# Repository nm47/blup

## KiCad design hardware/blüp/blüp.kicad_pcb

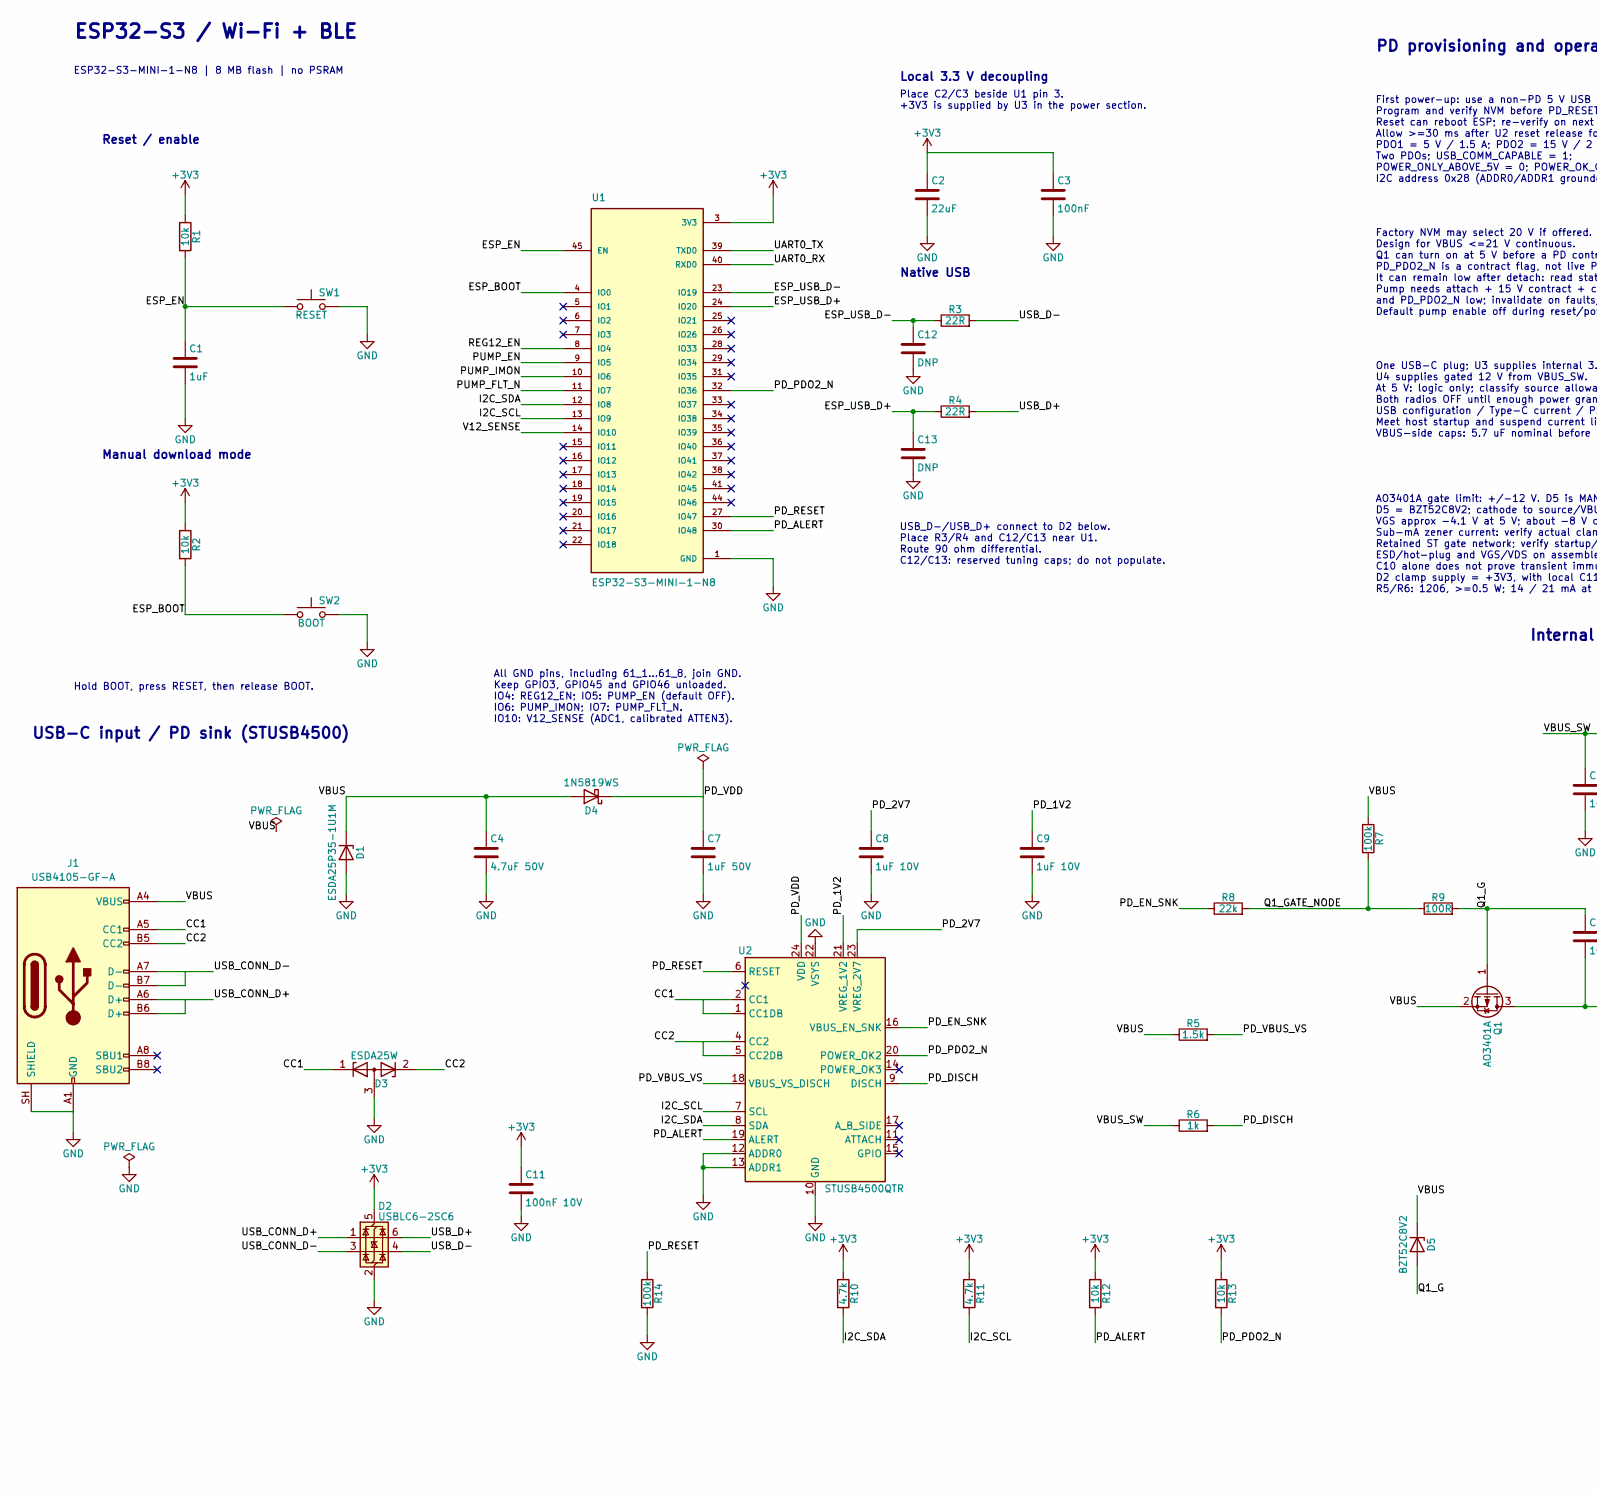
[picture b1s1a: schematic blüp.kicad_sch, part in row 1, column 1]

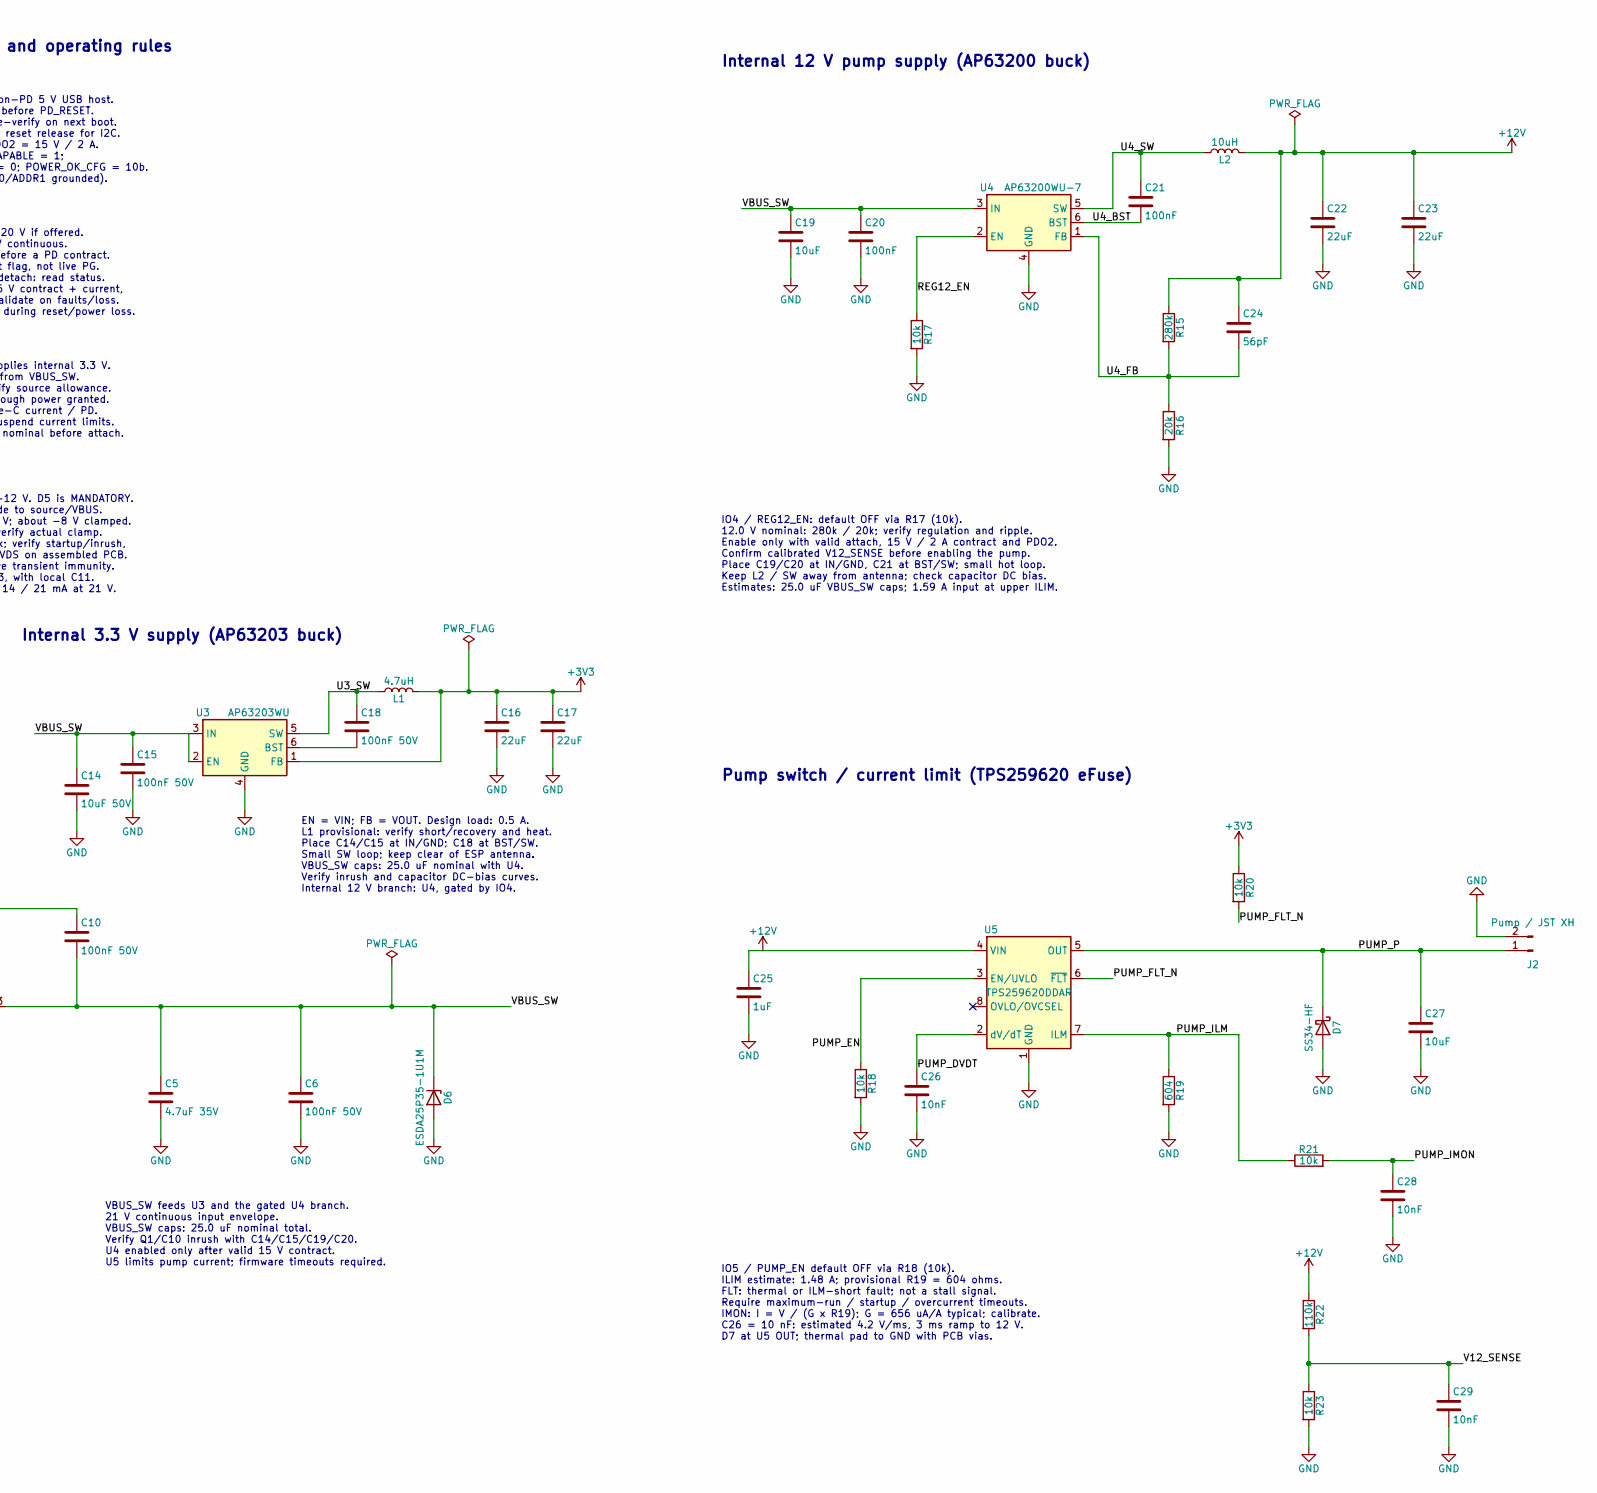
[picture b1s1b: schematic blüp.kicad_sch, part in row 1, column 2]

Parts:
C1: 1uF; C_0603_1608Metric; Tolerance 10%; Voltage 10V
C2, C16, C17: 22uF; C_0805_2012Metric; Tolerance 10%; Voltage 10V
C3: 100nF; C_0603_1608Metric; Tolerance 10%; Voltage 10V
C4: 4.7uF 50V; C_1206_3216Metric; Tolerance 10%; Voltage 50V
C5: 4.7uF 35V; C_1206_3216Metric; Tolerance 10%; Voltage 35V
C6, C10, C15, C18: 100nF 50V; C_0603_1608Metric; Tolerance 10%; Voltage 50V
C7: 1uF 50V; C_0805_2012Metric; Tolerance 10%; Voltage 50V
C8, C9: 1uF 10V; C_0603_1608Metric; Tolerance 10%; Voltage 10V
C11: 100nF 10V; C_0603_1608Metric; Tolerance 10%; Voltage 10V
C12, C13: DNP; C_0603_1608Metric
C14: 10uF 50V; C_1206_3216Metric; Tolerance 10%; Voltage 50V
C19: 10uF; C_1206_3216Metric; Tolerance 10%; Voltage 50V
C20, C21: 100nF; C_0603_1608Metric; Tolerance 10%; Voltage 50V
C22, C23: 22uF; C_1210_3225Metric; Tolerance 10%; Voltage 25V
C24: 56pF; C_0603_1608Metric; Tolerance 5%; Voltage 50V
C25: 1uF; C_0603_1608Metric; Tolerance 10%; Voltage 25V
C26, C28, C29: 10nF; C_0603_1608Metric; Tolerance 10%; Voltage 16V
C27: 10uF; C_1206_3216Metric; Tolerance 10%; Voltage 25V
D1, D6: ESDA25P35-1U1M; ST_QFN-2L_1.6x1.0mm; MPN ESDA25P35-1U1M; LCSC C1974707
D2: USBLC6-2SC6; SOT-23-6; MPN USBLC6-2SC6; LCSC C7519
D3: ESDA25W; SOT-323_SC-70; MPN ESDA25W; LCSC C2935152
D4: 1N5819WS; D_SOD-323; MPN 1N5819WS; LCSC C1884554
D5: BZT52C8V2; D_SOD-123; MPN BZT52C8V2-7-F
D7: SS34-HF; D_SMA; MPN SS34-HF
J1: USB4105-GF-A; USB_C_Receptacle_GCT_USB4105-xx-A_16P_TopMnt_Horizontal; MPN USB4105-GF-A
J2: Pump / JST XH; JST_XH_B2B-XH-A_1x02_P2.50mm_Vertical; MPN B2B-XH-A(LF)(SN)
L1: 4.7uH; L_Bourns-SRN4018; Tolerance 20%; MPN SRN4018-4R7M; LCSC C780206
L2: 10uH; L_Bourns_SRR1260; Tolerance 20%; MPN SRR1260-100M
Q1: AO3401A; SOT-23; MPN AO3401A; LCSC C15127
R1, R2: 10k; R_0603_1608Metric
R3, R4: 22R; R_0603_1608Metric
R5: 1.5k; R_1206_3216Metric; Tolerance 1%
R6: 1k; R_1206_3216Metric; Tolerance 1%
R7, R14: 100k; R_0603_1608Metric; Tolerance 1%
R8: 22k; R_0603_1608Metric; Tolerance 1%
R9: 100R; R_0603_1608Metric; Tolerance 1%
R10, R11: 4.7k; R_0603_1608Metric; Tolerance 1%
R12, R13, R17, R18, R20, R21, R23: 10k; R_0603_1608Metric; Tolerance 1%
R15: 280k; R_0603_1608Metric; Tolerance 1%
R16: 20k; R_0603_1608Metric; Tolerance 1%
R19: 604; R_0603_1608Metric; Tolerance 1%
R22: 110k; R_0603_1608Metric; Tolerance 1%
SW1: RESET; SW_Push_1P1T_XKB_TS-1187A; MPN TS-1187A-B-A-B; LCSC C318884
SW2: BOOT; SW_Push_1P1T_XKB_TS-1187A; MPN TS-1187A-B-A-B; LCSC C318884
U1: ESP32-S3-MINI-1-N8; XCVR_ESP32-S3-MINI-1-N8; MPN ESP32-S3-MINI-1-N8
U2: STUSB4500QTR; QFN-24-1EP_4x4mm_P0.5mm_EP2.7x2.7mm; MPN STUSB4500QTR; LCSC C2678061
U3: AP63203WU; TSOT-23-6; MPN AP63203WU-7; LCSC C780769
U4: AP63200WU-7; TSOT-23-6; MPN AP63200WU-7
U5: TPS259620DDAR; TI_SO-PowerPAD-8; MPN TPS259620DDAR

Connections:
+3V3: C2.1, C3.1, C11.1, C16.1, C17.1, D2.5 (VBUS), L1.2, R1.1, R2.1, R10.1, R11.1, R12.1, R13.1, R20.1, U1.3 (3V3), U3.1 (FB)
+12V: C22.1, C23.1, C24.1, C25.1, L2.2, R15.1, R22.1, U5.4 (VIN)
/CC1: D3.1 (K), J1.A5 (CC1), U2.1 (CC1DB), U2.2 (CC1)
/CC2: D3.2 (K), J1.B5 (CC2), U2.4 (CC2), U2.5 (CC2DB)
/ESP_BOOT: R2.2, SW2.1, U1.4 (IO0)
/ESP_EN: C1.1, R1.2, SW1.1, U1.45 (EN)
/ESP_USB_D+: C13.1, R4.1, U1.24 (IO20)
/ESP_USB_D-: C12.1, R3.1, U1.23 (IO19)
/I2C_SCL: R11.2, U1.13 (IO9), U2.7 (SCL)
/I2C_SDA: R10.2, U1.12 (IO8), U2.8 (SDA)
/PD_1V2: C9.1, U2.21 (VREG_1V2)
/PD_2V7: C8.1, U2.23 (VREG_2V7)
/PD_ALERT: R12.2, U1.30 (IO48), U2.19 (ALERT)
/PD_DISCH: R6.2, U2.9 (DISCH)
/PD_EN_SNK: R8.1, U2.16 (VBUS_EN_SNK)
/PD_PDO2_N: R13.2, U1.32 (IO36), U2.20 (POWER_OK2)
/PD_RESET: R14.1, U1.27 (IO47), U2.6 (RESET)
/PD_VBUS_VS: R5.2, U2.18 (VBUS_VS_DISCH)
/PD_VDD: C7.1, D4.1 (K), U2.24 (VDD)
/PUMP_DVDT: C26.1, U5.2 (dV/dT)
/PUMP_EN: R18.1, U1.9 (IO5), U5.3 (EN/UVLO)
/PUMP_FLT_N: R20.2, U1.11 (IO7), U5.6 (~FLT)
/PUMP_ILM: R19.1, R21.1, U5.7 (ILM)
/PUMP_IMON: C28.1, R21.2, U1.10 (IO6)
/PUMP_P: C27.1, D7.1 (K), J2.1, U5.5 (OUT)
/Q1_G: C10.1, D5.2 (A), Q1.1 (G), R9.2
/Q1_GATE_NODE: R7.2, R8.2, R9.1
/REG12_EN: R17.1, U1.8 (IO4), U4.2 (EN)
/U3_SW: C18.1, L1.1, U3.5 (SW)
/U4_BST: C21.2, U4.6 (BST)
/U4_FB: C24.2, R15.2, R16.1, U4.1 (FB)
/U4_SW: C21.1, L2.1, U4.5 (SW)
/UART0_RX: U1.40 (RXD0)
/UART0_TX: U1.39 (TXD0)
/USB_CONN_D+: D2.1 (I/O1), J1.A6 (D+), J1.B6 (D+)
/USB_CONN_D-: D2.3 (I/O2), J1.A7 (D-), J1.B7 (D-)
/USB_D+: D2.6 (I/O1), R4.2
/USB_D-: D2.4 (I/O2), R3.2
/V12_SENSE: C29.1, R22.2, R23.1, U1.14 (IO10)
/VBUS: C4.1, D1.1 (K), D4.2 (A), D5.1 (K), J1.A4 (VBUS), J1.A9 (VBUS), J1.B4 (VBUS), J1.B9 (VBUS), Q1.2 (S), R5.1, R7.1
/VBUS_SW: C5.1, C6.1, C10.2, C14.1, C15.1, C19.1, C20.1, D6.1 (K), Q1.3 (D), R6.1, U3.2 (EN), U3.3 (IN), U4.3 (IN)
GND: C1.2, C2.2, C3.2, C4.2, C5.2, C6.2, C7.2, C8.2, C9.2, C11.2, C12.2, C13.2, C14.2, C15.2, C16.2, C17.2, C19.2, C20.2, C22.2, C23.2, C25.2, C26.2, C27.2, C28.2, C29.2, D1.2 (A), D2.2 (GND), D3.3 (A), D6.2 (A), D7.2 (A), J1.A1 (GND), J1.A12 (GND), J1.B1 (GND), J1.B12 (GND), J1.SH (SHIELD), J2.2, R14.2, R16.2, R17.2, R18.2, R19.2, R23.2, SW1.2, SW2.2, U1.1 (GND), U1.2 (GND), U1.42 (GND), U1.43 (GND), U1.46 (GND), U1.47 (GND), U1.48 (GND), U1.49 (GND), U1.50 (GND), U1.51 (GND), U1.52 (GND), U1.53 (GND), U1.54 (GND), U1.55 (GND), U1.56 (GND), U1.57 (GND), U1.58 (GND), U1.59 (GND), U1.60 (GND), U1.61 (GND), U1.61_1 (GND), U1.61_2 (GND), U1.61_3 (GND), U1.61_4 (GND), U1.61_5 (GND), U1.61_6 (GND), U1.61_7 (GND), U1.61_8 (GND), U1.62 (GND), U1.63 (GND), U1.64 (GND), U1.65 (GND), U2.10 (GND), U2.12 (ADDR0), U2.13 (ADDR1), U2.22 (VSYS), U2.25 (GND), U3.4 (GND), U4.4 (GND), U5.1 (GND), U5.9 (GND)
unnamed: C18.2, U3.6 (BST)

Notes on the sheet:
Local 3.3 V decoupling
ESP32-S3-MINI-1-N8 | 8 MB flash | no PSRAM
Reset / enable
ESP32-S3 / Wi-Fi + BLE
Native USB
Manual download mode
Hold BOOT, press RESET, then release BOOT.
PD provisioning and operating rules
USB-C input / PD sink (STUSB4500)
USB_D-/USB_D+ connect to D2 below. Place R3/R4 and C12/C13 near U1. Route 90 ohm differential. C12/C13: reserved tuning caps; do not populate.
First power-up: use a non-PD 5 V USB host. Program and verify NVM before PD_RESET. Reset can reboot ESP; re-verify on next boot. Allow >=30 ms after U2 reset release for I2C. PDO1 = 5 V / 1.5 A; PDO2 = 15 V / 2 A. Two PDOs; USB_COMM_CAPABLE = 1; POWER_ONLY_ABOVE_5V = 0; POWER_OK_CFG = 10b. I2C addr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
Factory NVM may select 20 V if offered. Design for VBUS <=21 V continuous. Q1 can turn on at 5 V before a PD contract. PD_PDO2_N is a contract flag, not live PG. It can remain low after detach: read status. Pump needs attach + 15 V contract + current, and PD_PDO2_N low; invalidate on faults/loss. D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
AO3401A gate limit: +/-12 V. D5 is MANDATORY. D5 = BZT52C8V2; cathode to source/VBUS. VGS approx -4.1 V at 5 V; about -8 V clamped. Sub-mA zener current: verify actual clamp. Retained ST gate network; verify startup/inrush, ESD/hot-plug and VGS/VDS on assembled PCB. C10 alone does not prove transie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
Internal 3.3 V supply (AP63203 buck)
Place C2/C3 beside U1 pin 3. +3V3 is supplied by U3 in the power section.
All GND pins, including 61_1...61_8, join GND. Keep GPIO3, GPIO45 and GPIO46 unloaded. IO4: REG12_EN; IO5: PUMP_EN (default OFF). IO6: PUMP_IMON; IO7: PUMP_FLT_N. IO10: V12_SENSE (ADC1, calibrated ATTEN3).
EN = VIN; FB = VOUT. Design load: 0.5 A. L1 provisional: verify short/recovery and heat. Place C14/C15 at IN/GND; C18 at BST/SW. Small SW loop; keep clear of ESP antenna. VBUS_SW caps: 25.0 uF nominal with U4. Verify inrush and capacitor DC-bias curves. Internal 12 V branch: U4, gated by IO4.
One USB-C plug; U3 supplies internal 3.3 V. U4 supplies gated 12 V from VBUS_SW. At 5 V: logic only; classify source allowance. Both radios OFF until enough power granted. USB configuration / Type-C current / PD. Meet host startup and suspend current limits. VBUS-side caps: 5.7 uF nominal before at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
VBUS_SW feeds U3 and the gated U4 branch. 21 V continuous input envelope. VBUS_SW caps: 25.0 uF nominal total. Verify Q1/C10 inrush with C14/C15/C19/C20. U4 enabled only after valid 15 V contract. U5 limits pump current; firmware timeouts required.
Internal 12 V pump supply (AP63200 buck)
IO4 / REG12_EN: default OFF via R17 (10k). 12.0 V nominal: 280k / 20k; verify regulation and ripple. Enable only with valid attach, 15 V / 2 A contract and PDO2. Confirm calibrated V12_SENSE before enabling the pump. Place C19/C20 at IN/GND, C21 at BST/SW; small hot loop. Keep L2 / SW away from ant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
Pump switch / current limit (TPS259620 eFuse)
IO5 / PUMP_EN default OFF via R18 (10k). ILIM estimate: 1.48 A; provisional R19 = 604 ohms. FLT: thermal or ILM-short fault; not a stall signal. Require maximum-run / startup / overcurrent timeouts. IMON: I = V / (G x R19); G = 656 uA/A typical; calibrate. C26 = 10 nF: estimated 4.2 V/ms, 3 ms ramp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

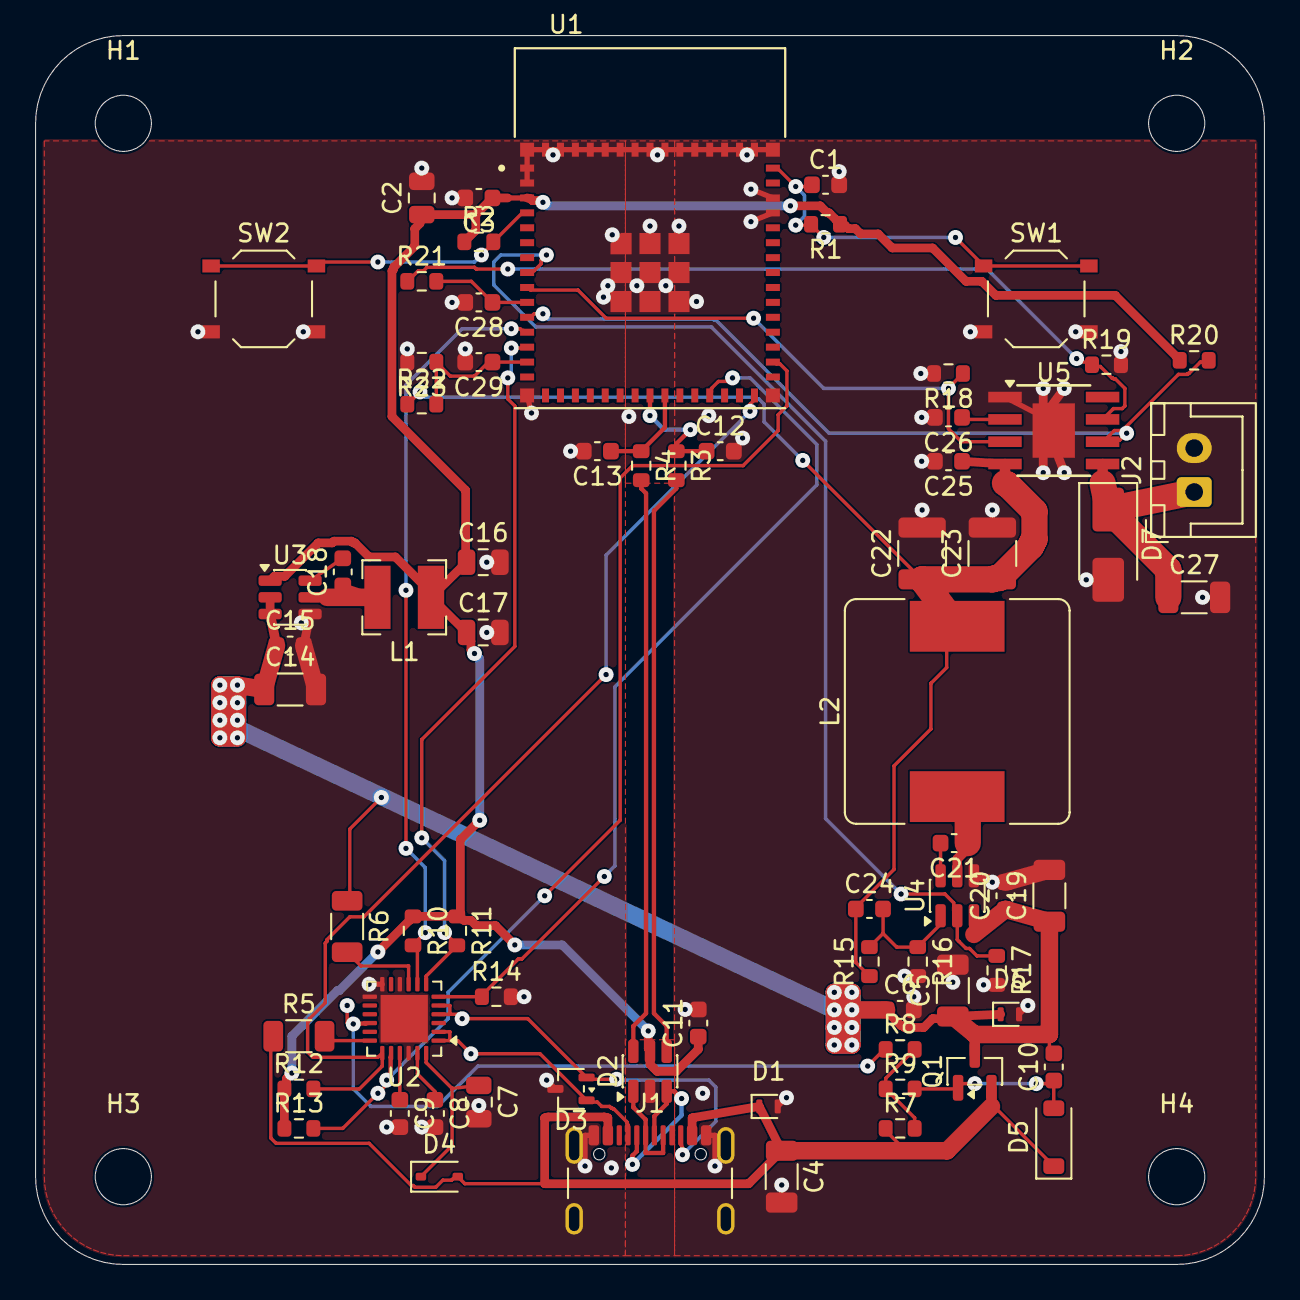
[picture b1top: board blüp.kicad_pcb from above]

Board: 4 copper layers, 70.0 x 70.0 mm, 75 parts (0 on the bottom side), 41 nets.

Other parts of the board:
H1, H2, H3, H4: MountingHole_3.2mm_M3
